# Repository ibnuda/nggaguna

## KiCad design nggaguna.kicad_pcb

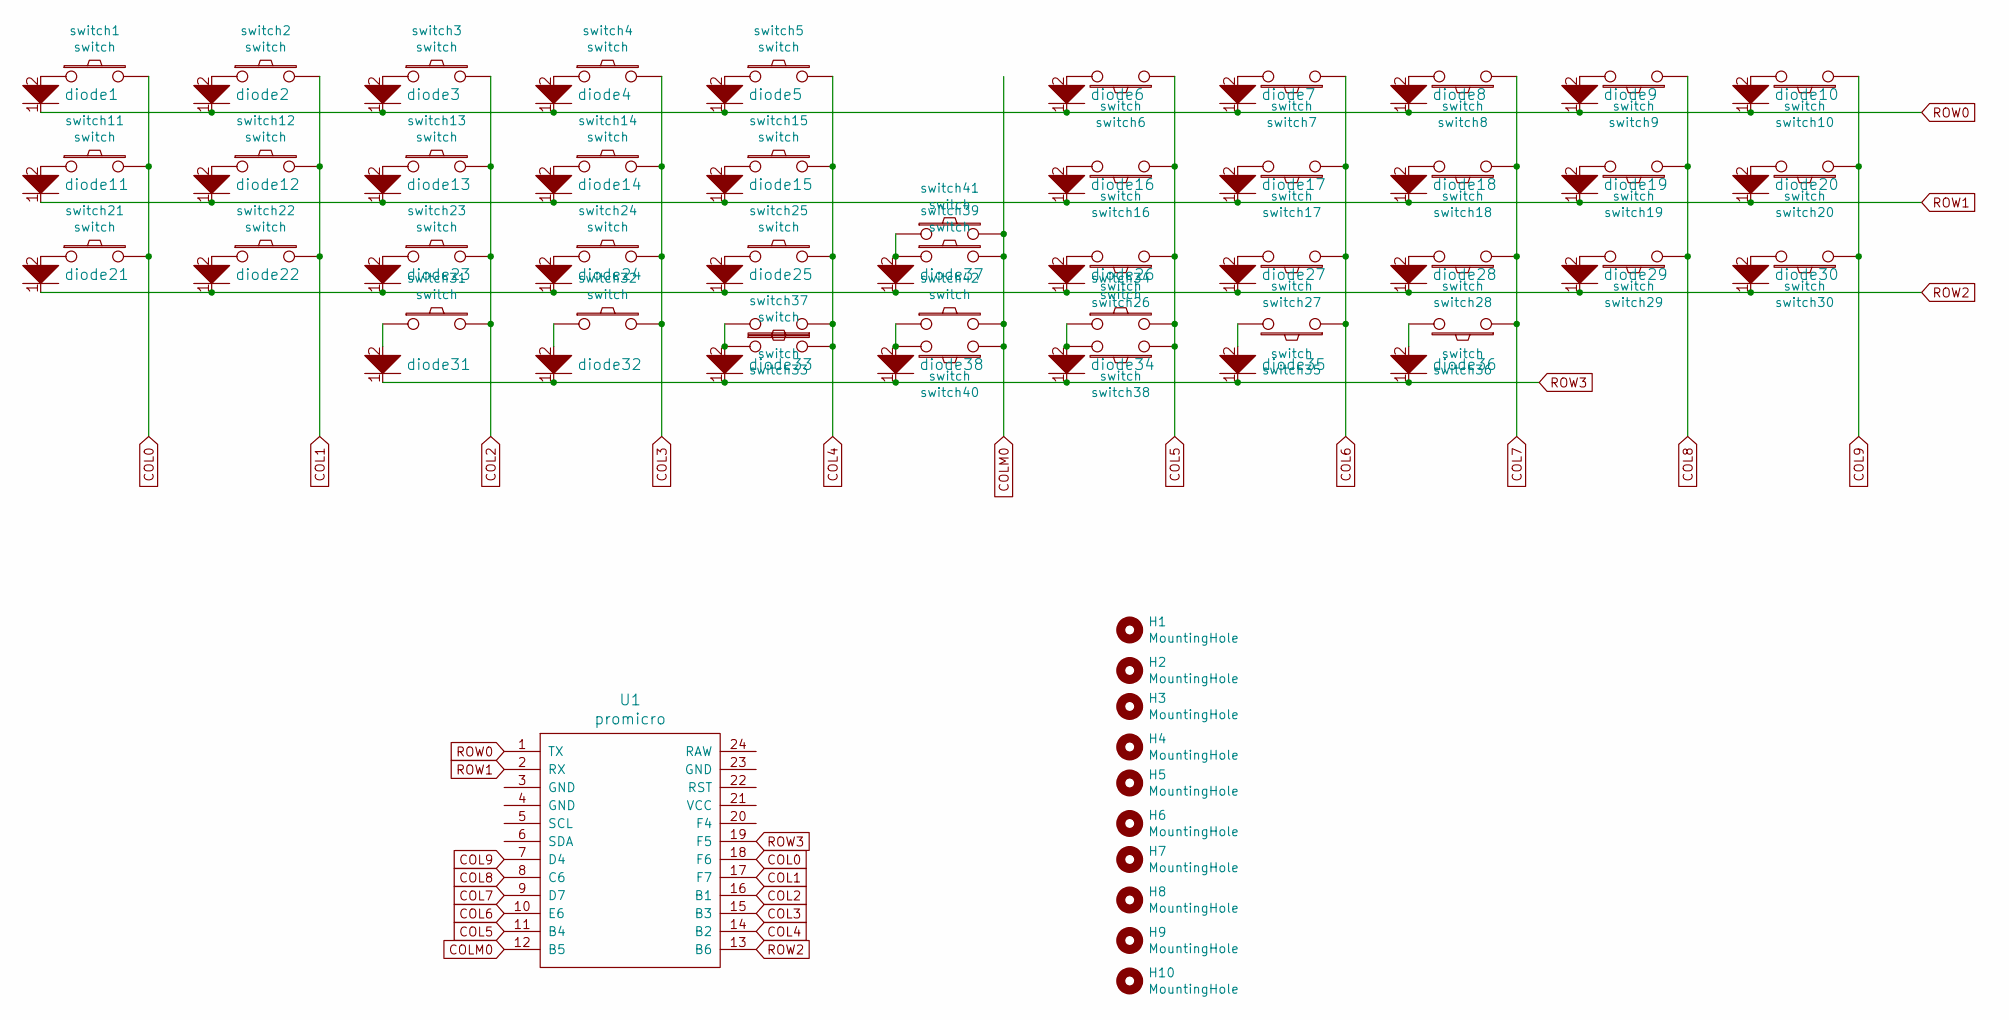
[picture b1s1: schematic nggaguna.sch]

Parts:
H1, H2, H3, H4, H5, H6, H7, H8, H9, H10: MountingHole; hole-m2-pcb
U1: promicro
diode1, diode2, diode3, diode4, diode5, diode6, diode7, diode8, diode9, diode10, diode11, diode12, diode13, diode14, diode15, diode16, diode17, diode18, diode19, diode20, diode21, diode22, diode23, diode24, diode25, diode26, diode27, diode28, diode29, diode30, diode31, diode32, diode33, diode34, diode35, diode36, diode37, diode38: diode
switch1, switch2, switch3, switch4, switch5, switch6, switch7, switch8, switch9, switch10, switch11, switch12, switch13, switch14, switch15, switch16, switch17, switch18, switch19, switch20, switch21, switch22, switch23, switch24, switch25, switch26, switch27, switch28, switch29, switch30, switch31, switch32, switch33, switch34, switch35, switch36, switch39, switch40: switch; 100-minimal
switch37, switch38, switch41, switch42: switch; 200-minimal

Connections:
COL0: U1.18 (F6), switch1.2, switch11.2, switch21.2
COL1: U1.17 (F7), switch2.2, switch12.2, switch22.2
COL2: U1.16 (B1), switch3.2, switch13.2, switch23.2, switch31.2
COL3: U1.15 (B3), switch4.2, switch14.2, switch24.2, switch32.2
COL4: U1.14 (B2), switch5.2, switch15.2, switch25.2, switch33.1, switch37.2
COL5: U1.11 (B4), switch6.1, switch16.1, switch26.1, switch34.2, switch38.1
COL6: U1.10 (E6), switch7.1, switch17.1, switch27.1, switch35.1
COL7: U1.9 (D7), switch8.1, switch18.1, switch28.1, switch36.1
COL8: U1.8 (C6), switch9.1, switch19.1, switch29.1
COL9: U1.7 (D4), switch10.1, switch20.1, switch30.1
COLM0: U1.12 (B5), switch39.2, switch40.1, switch41.2, switch42.2
unnamed: diode1.2, switch1.1
unnamed: diode2.2, switch2.1
unnamed: diode3.2, switch3.1
unnamed: diode4.2, switch4.1
unnamed: diode5.2, switch5.1
unnamed: diode6.2, switch6.2
unnamed: diode7.2, switch7.2
unnamed: diode8.2, switch8.2
unnamed: diode9.2, switch9.2
unnamed: diode10.2, switch10.2
unnamed: diode11.2, switch11.1
unnamed: diode12.2, switch12.1
unnamed: diode13.2, switch13.1
unnamed: diode14.2, switch14.1
unnamed: diode15.2, switch15.1
unnamed: diode16.2, switch16.2
unnamed: diode17.2, switch17.2
unnamed: diode18.2, switch18.2
unnamed: diode19.2, switch19.2
unnamed: diode20.2, switch20.2
unnamed: diode21.2, switch21.1
unnamed: diode22.2, switch22.1
unnamed: diode23.2, switch23.1
unnamed: diode24.2, switch24.1
unnamed: diode25.2, switch25.1
unnamed: diode26.2, switch26.2
unnamed: diode27.2, switch27.2
unnamed: diode28.2, switch28.2
unnamed: diode29.2, switch29.2
unnamed: diode30.2, switch30.2
unnamed: diode31.2, switch31.1
unnamed: diode32.2, switch32.1
unnamed: diode33.2, switch33.2, switch37.1
unnamed: diode34.2, switch34.1, switch38.2
unnamed: diode35.2, switch35.2
unnamed: diode36.2, switch36.2
unnamed: diode37.2, switch39.1, switch41.1
unnamed: diode38.2, switch40.2, switch42.1
ROW0: U1.1 (TX), diode1.1, diode2.1, diode3.1, diode4.1, diode5.1, diode6.1, diode7.1, diode8.1, diode9.1, diode10.1
ROW1: U1.2 (RX), diode11.1, diode12.1, diode13.1, diode14.1, diode15.1, diode16.1, diode17.1, diode18.1, diode19.1, diode20.1
ROW2: U1.13 (B6), diode21.1, diode22.1, diode23.1, diode24.1, diode25.1, diode26.1, diode27.1, diode28.1, diode29.1, diode30.1, diode37.1
ROW3: U1.19 (F5), diode31.1, diode32.1, diode33.1, diode34.1, diode35.1, diode36.1, diode38.1

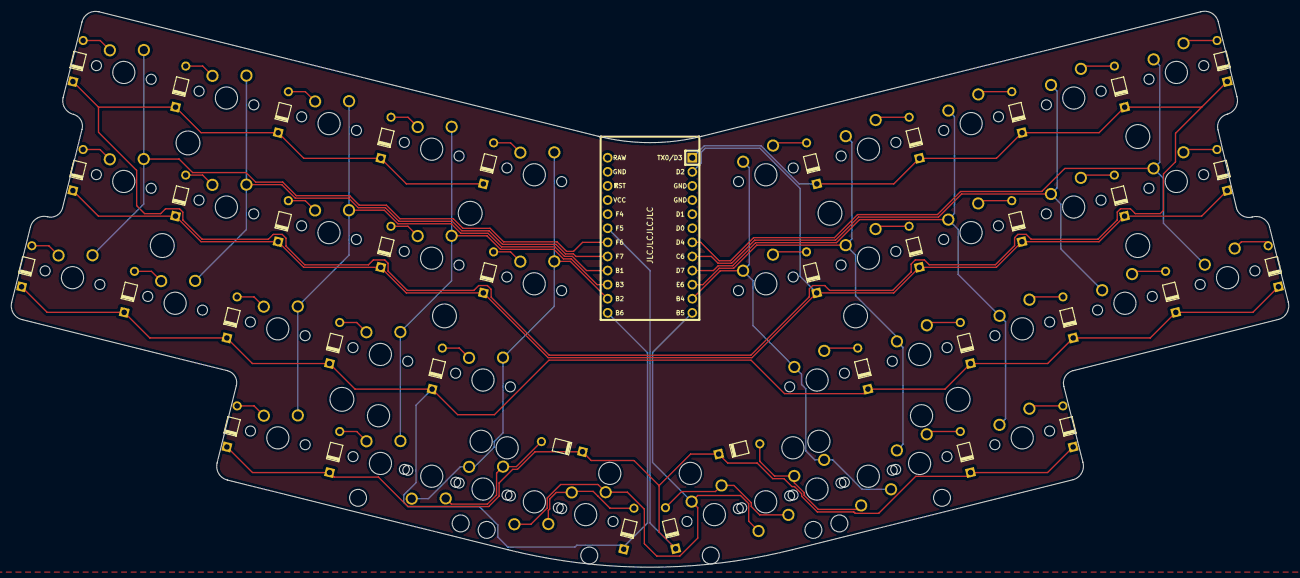
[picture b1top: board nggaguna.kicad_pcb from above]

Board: 2 copper layers, 230.1 x 100.1 mm, 91 parts (1 on the bottom side), 53 nets.

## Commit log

2021-01-24 selesai.
2021-01-24 lisensi dan readme.
2021-01-25 ez plate.
2021-01-26 3d model for promicro.
2021-02-13 revamp
